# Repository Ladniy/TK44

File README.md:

Wireless ergo unibody split keyboard, based on [Holyiot-18010 (nRF52840)](http://www.holyiot.com/tp/2019042516322180424.pdf) module.

* __Author:__ [@ladniys (Telegram)](https://t.me/ladniys) [u/Ladniy (Reddit)](https://reddit.com/u/Ladniy)
* __Layout:__ [keyboard-layout-editor.com](http://www.keyboard-layout-editor.com/#/gists/4b6c2af67148f58ddd6c6b2976c4370f) (actually same as [Jian's](https://github.com/KGOH/Jian-Info))
* __Hardware Availability:__ [Open Source](https://github.com/Ladniy/TK44/releases/tag/v1.0.0)
* __Firmware:__ [ZMK](https://zmk.dev/)

Check out [wiki-page](https://github.com/Ladniy/TK44/wiki) for more information.

## Photos

**See more photos on [Imgur](https://imgur.com/a/DaCdFm3)**

## Project status

**The keyboard is fully functional, no problems were noticed.**

## License

This project is licensed under a [CERN-OHL-P v2.0](https://ohwr.org/project/cernohl/wikis/Documents/CERN-OHL-version-2).

Feel free to use, share, modify or even sell TK44!

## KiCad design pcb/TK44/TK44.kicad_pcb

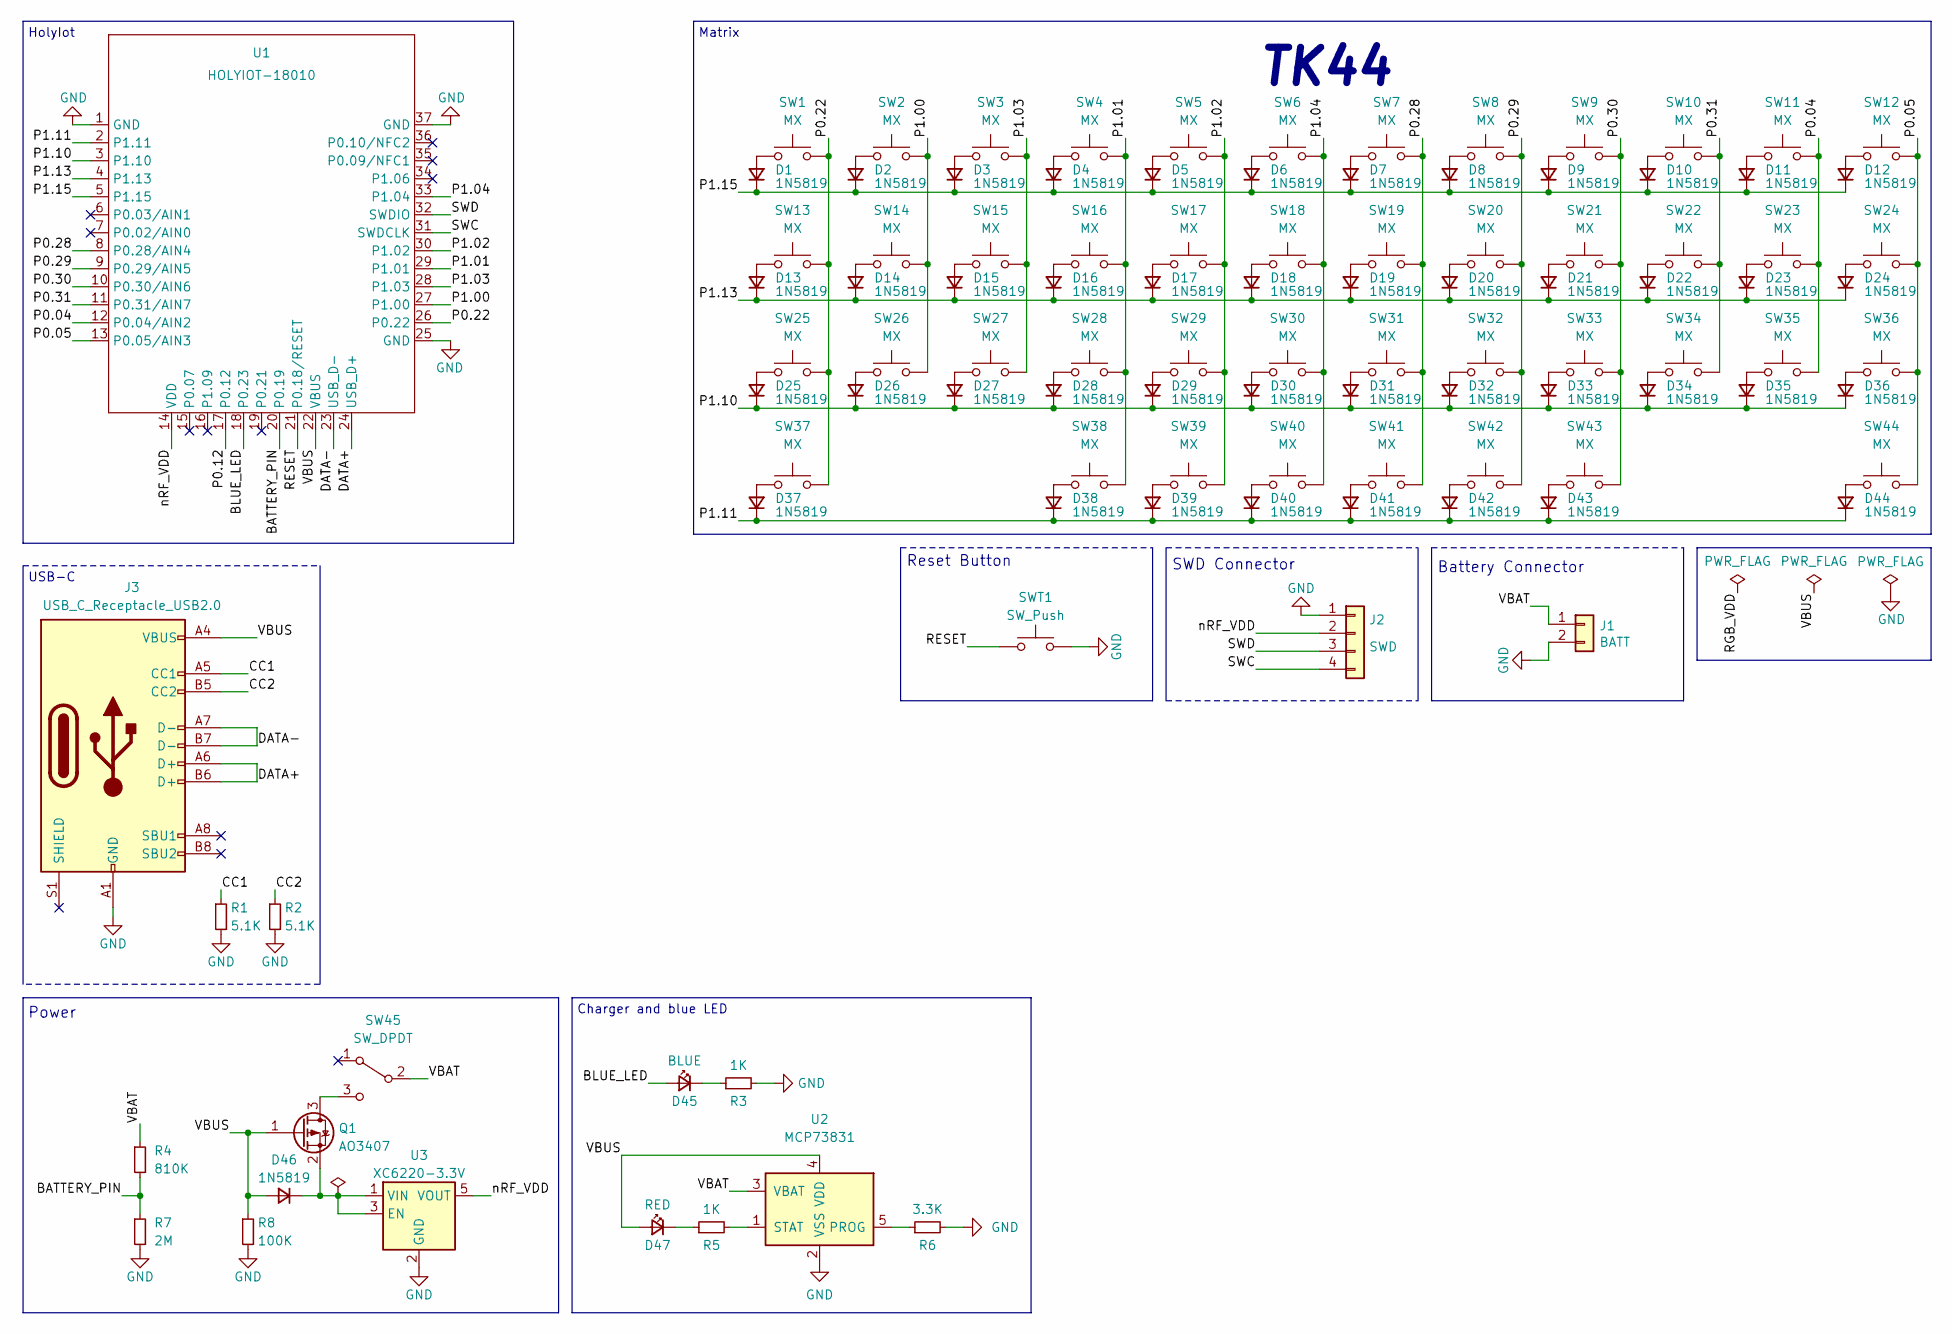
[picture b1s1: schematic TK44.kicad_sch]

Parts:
D1, D2, D3, D4, D5, D6, D7, D8, D9, D10, D11, D12, D13, D14, D15, D16, D17, D18, D19, D20, D21, D22, D23, D24, D25, D26, D27, D28, D29, D30, D31, D32, D33, D34, D35, D36, D37, D38, D39, D40, D41, D42, D43, D44, D46: 1N5819; D_SOD-123
D45: BLUE; LED_0603
D47: RED; LED_0603
J1: BATT; Battery_Connector
J2: SWD; Connector_THT_1x4_2.54
J3: USB_C_Receptacle_USB2.0; USB-C-C168688
Q1: AO3407; SOT-23
R1, R2: 5.1K; R_0603
R3, R5: 1K; R_0603
R4: 810K; R_0603
R6: 3.3K; R_0603
R7: 2M; R_0603
R8: 100K; R_0603
SW1, SW2, SW3, SW4, SW5, SW6, SW7, SW8, SW9, SW10, SW11, SW12, SW13, SW14, SW15, SW16, SW17, SW18, SW19, SW20, SW21, SW22, SW23, SW24, SW25, SW26, SW27, SW28, SW29, SW30, SW31, SW32, SW33, SW34, SW35, SW36, SW37, SW39, SW42, SW44: MX; Switch_Mx_Hotswap_1u
SW38, SW40, SW41, SW43: MX; Switch_Mx_Hotswap_1.25u
SW45: SW_DPDT; MSK-12C02
SWT1: SW_Push; K2-1187SQ
U1: HOLYIOT-18010; Holyiot-18010-nRF52840
U2: MCP73831; SOT-23-5
U3: XC6220-3.3V; SOT-23-5

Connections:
/BATTERY_PIN: R4.2, R7.1, U1.20 (P0.19)
/BLUE_LED: D45.2 (A), U1.18 (P0.23)
/CC1: J3.A5 (CC1), R1.1
/CC2: J3.B5 (CC2), R2.1
/DATA+: J3.A6 (D+), J3.B6 (D+), U1.24 (USB_D+)
/DATA-: J3.A7 (D-), J3.B7 (D-), U1.23 (USB_D-)
/P0.04: SW11.2, SW23.2, SW35.2, U1.12 (P0.04/AIN2)
/P0.05: SW12.2, SW24.2, SW36.2, SW44.2, U1.13 (P0.05/AIN3)
/P0.12: U1.17 (P0.12)
/P0.22: SW1.2, SW13.2, SW25.2, SW37.2, U1.26 (P0.22)
/P0.28: SW7.2, SW19.2, SW31.2, SW41.2, U1.8 (P0.28/AIN4)
/P0.29: SW8.2, SW20.2, SW32.2, SW42.2, U1.9 (P0.29/AIN5)
/P0.30: SW9.2, SW21.2, SW33.2, SW43.2, U1.10 (P0.30/AIN6)
/P0.31: SW10.2, SW22.2, SW34.2, U1.11 (P0.31/AIN7)
/P1.00: SW2.2, SW14.2, SW26.2, U1.27 (P1.00)
/P1.01: SW4.2, SW16.2, SW28.2, SW38.2, U1.29 (P1.01)
/P1.02: SW5.2, SW17.2, SW29.2, SW39.2, U1.30 (P1.02)
/P1.03: SW3.2, SW15.2, SW27.2, U1.28 (P1.03)
/P1.04: SW6.2, SW18.2, SW30.2, SW40.2, U1.33 (P1.04)
/P1.10: D25.1 (K), D26.1 (K), D27.1 (K), D28.1 (K), D29.1 (K), D30.1 (K), D31.1 (K), D32.1 (K), D33.1 (K), D34.1 (K), D35.1 (K), D36.1 (K), U1.3 (P1.10)
/P1.11: D37.1 (K), D38.1 (K), D39.1 (K), D40.1 (K), D41.1 (K), D42.1 (K), D43.1 (K), D44.1 (K), U1.2 (P1.11)
/P1.13: D13.1 (K), D14.1 (K), D15.1 (K), D16.1 (K), D17.1 (K), D18.1 (K), D19.1 (K), D20.1 (K), D21.1 (K), D22.1 (K), D23.1 (K), D24.1 (K), U1.4 (P1.13)
/P1.15: D1.1 (K), D2.1 (K), D3.1 (K), D4.1 (K), D5.1 (K), D6.1 (K), D7.1 (K), D8.1 (K), D9.1 (K), D10.1 (K), D11.1 (K), D12.1 (K), U1.5 (P1.15)
/RESET: SWT1.1, U1.21 (P0.18/RESET)
/SWC: J2.4, U1.31 (SWDCLK)
/SWD: J2.3, U1.32 (SWDIO)
/VBAT: J1.1, R4.1, SW45.2, U2.3 (VBAT)
/VBUS: D46.2 (A), D47.2 (A), J3.A4 (VBUS), J3.A9 (VBUS), J3.B4 (VBUS), J3.B9 (VBUS), Q1.1 (G), R8.1, U1.22 (VBUS), U2.4 (VDD)
/nRF_VDD: J2.2, U1.14 (VDD), U3.5 (VOUT)
GND: J1.2, J2.1, J3.A1 (GND), J3.A12 (GND), J3.B1 (GND), J3.B12 (GND), R1.2, R2.2, R3.2, R6.2, R7.2, R8.2, SWT1.2, U1.1 (GND), U1.25 (GND), U1.37 (GND), U2.2 (VSS), U3.2 (GND)
unnamed: D1.2 (A), SW1.1
unnamed: D2.2 (A), SW2.1
unnamed: D3.2 (A), SW3.1
unnamed: D4.2 (A), SW4.1
unnamed: D5.2 (A), SW5.1
unnamed: D6.2 (A), SW6.1
unnamed: D7.2 (A), SW7.1
unnamed: D8.2 (A), SW8.1
unnamed: D9.2 (A), SW9.1
unnamed: D10.2 (A), SW10.1
unnamed: D11.2 (A), SW11.1
unnamed: D12.2 (A), SW12.1
unnamed: D13.2 (A), SW13.1
unnamed: D14.2 (A), SW14.1
unnamed: D15.2 (A), SW15.1
unnamed: D16.2 (A), SW16.1
unnamed: D17.2 (A), SW17.1
unnamed: D18.2 (A), SW18.1
unnamed: D19.2 (A), SW19.1
unnamed: D20.2 (A), SW20.1
unnamed: D21.2 (A), SW21.1
unnamed: D22.2 (A), SW22.1
unnamed: D23.2 (A), SW23.1
unnamed: D24.2 (A), SW24.1
unnamed: D25.2 (A), SW25.1
unnamed: D26.2 (A), SW26.1
unnamed: D27.2 (A), SW27.1
unnamed: D28.2 (A), SW28.1
unnamed: D29.2 (A), SW29.1
unnamed: D30.2 (A), SW30.1
unnamed: D31.2 (A), SW31.1
unnamed: D32.2 (A), SW32.1
unnamed: D33.2 (A), SW33.1
unnamed: D34.2 (A), SW34.1
unnamed: D35.2 (A), SW35.1
unnamed: D36.2 (A), SW36.1
unnamed: D37.2 (A), SW37.1
unnamed: D38.2 (A), SW38.1
unnamed: D39.2 (A), SW39.1
unnamed: D40.2 (A), SW40.1
unnamed: D41.2 (A), SW41.1
unnamed: D42.2 (A), SW42.1
unnamed: D43.2 (A), SW43.1
unnamed: D44.2 (A), SW44.1
unnamed: D45.1 (K), R3.1
unnamed: D46.1 (K), Q1.2 (S), U3.1 (VIN), U3.3 (EN)
unnamed: D47.1 (K), R5.1
unnamed: Q1.3 (D), SW45.3
unnamed: R5.2, U2.1 (STAT)
unnamed: R6.1, U2.5 (PROG)

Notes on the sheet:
HolyIot
USB-C
Power
TK44
SWD Сonnector
Reset Button
Battery Сonnector
Charger and blue LED
Matrix

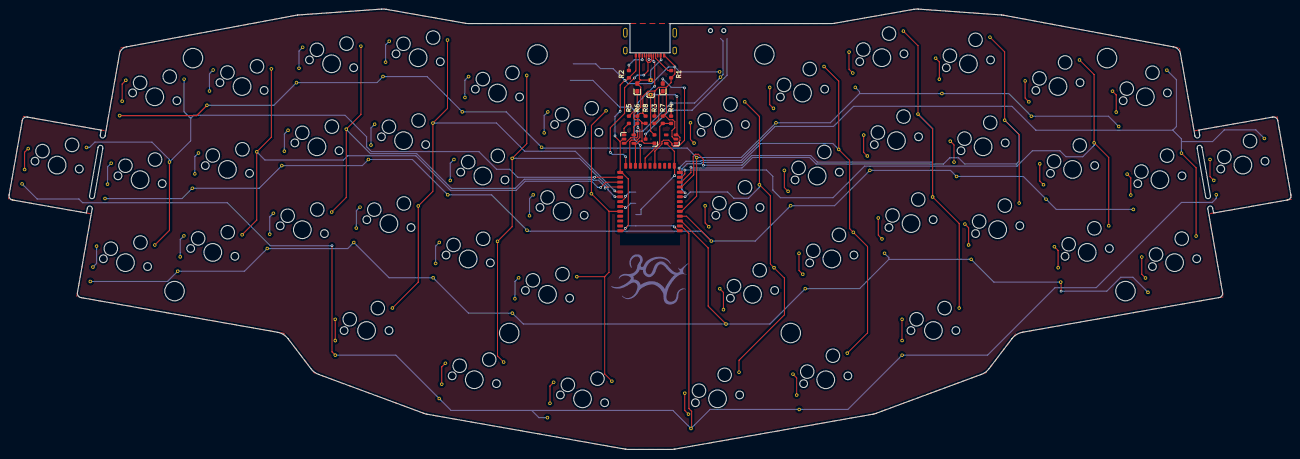
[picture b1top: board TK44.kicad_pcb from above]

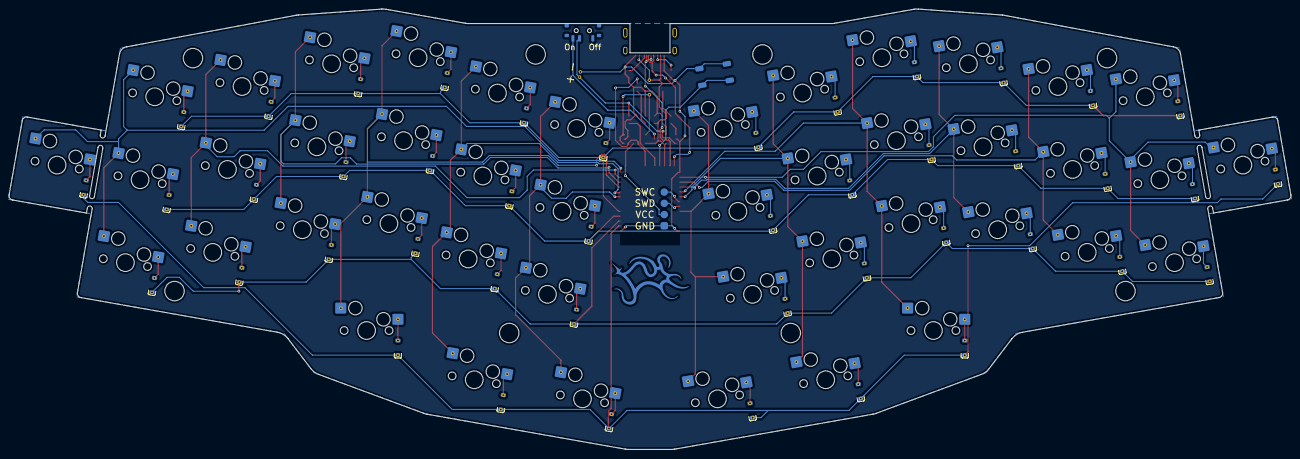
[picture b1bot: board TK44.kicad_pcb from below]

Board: 2 copper layers, 289.9 x 99.6 mm, 117 parts (48 on the bottom side), 79 nets.

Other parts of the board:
H1, H2, H3, H4, H5, H6, H7, H8: Hole_Mount_M4
LOGO1: LOGO; logo

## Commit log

2022-03-28 Update top header
2022-03-28 Add symbol lib
2022-03-28 Create project & complete schematic
2022-03-28 Plot schematic
2022-04-06 No comment /////
2022-04-06 Fix silkscreen clearance
2022-04-06 Fix DRC errors and silk overlapping
2022-04-06 Add some text
2022-04-06 Update logo footprint & refill zones
2022-04-06 Ad gitignore file
2022-04-07 Design fr-4 bottom
2022-04-07 Design fr-4 plate
2022-04-07 Remove old backups
2022-04-07 Clean up
2022-04-07 Remove hidden autocad files
2022-04-08 Plot gerbers
2022-04-19 Plot new gerbers
2022-04-19 Just a little fix
2022-04-19 Fix breakoff width
2022-04-19 Plot new schematic pdf
2022-05-27 Change battery pin
2022-05-27 Route track for battery pin
2022-07-18 Update gerbers
2022-07-18 Update logo footprint and pdf of schematic
2022-07-18 Design dxf files for case
2022-07-18 Update PCB
2022-08-26 prl update
2022-08-26 Create template
2022-08-28 Change link for title image and others
2022-08-28 Update link for wiki page
2022-08-28 Add photos header
2022-08-28 Remove gerbers files and rename zip archive
2022-08-28 Move files for case
2022-08-28 Create global misc catalog and move schematic pdf there
2022-08-28 Little clean up
2022-08-28 Add firmware and ibom files
2022-08-28 Change license of project
2022-08-28 Add rule for ignoring .DS_Store
2022-08-28 Update link for release
2023-01-19 Little change in silkscreen
2023-02-24 Fix readme
2023-10-31 docs: update readme file
2023-10-31 docs: change license, now project fully open source
2023-10-31 docs: fix keyboard name
